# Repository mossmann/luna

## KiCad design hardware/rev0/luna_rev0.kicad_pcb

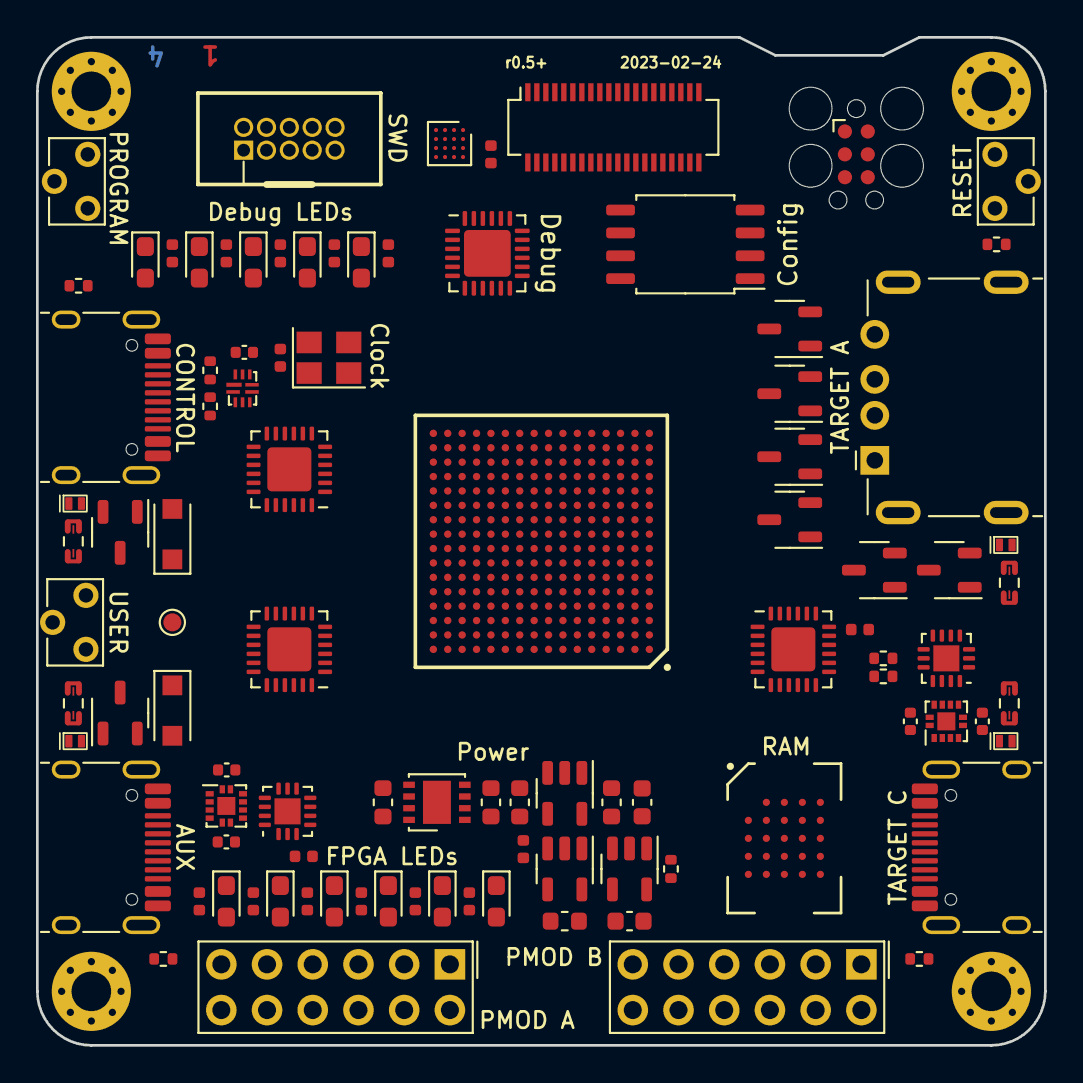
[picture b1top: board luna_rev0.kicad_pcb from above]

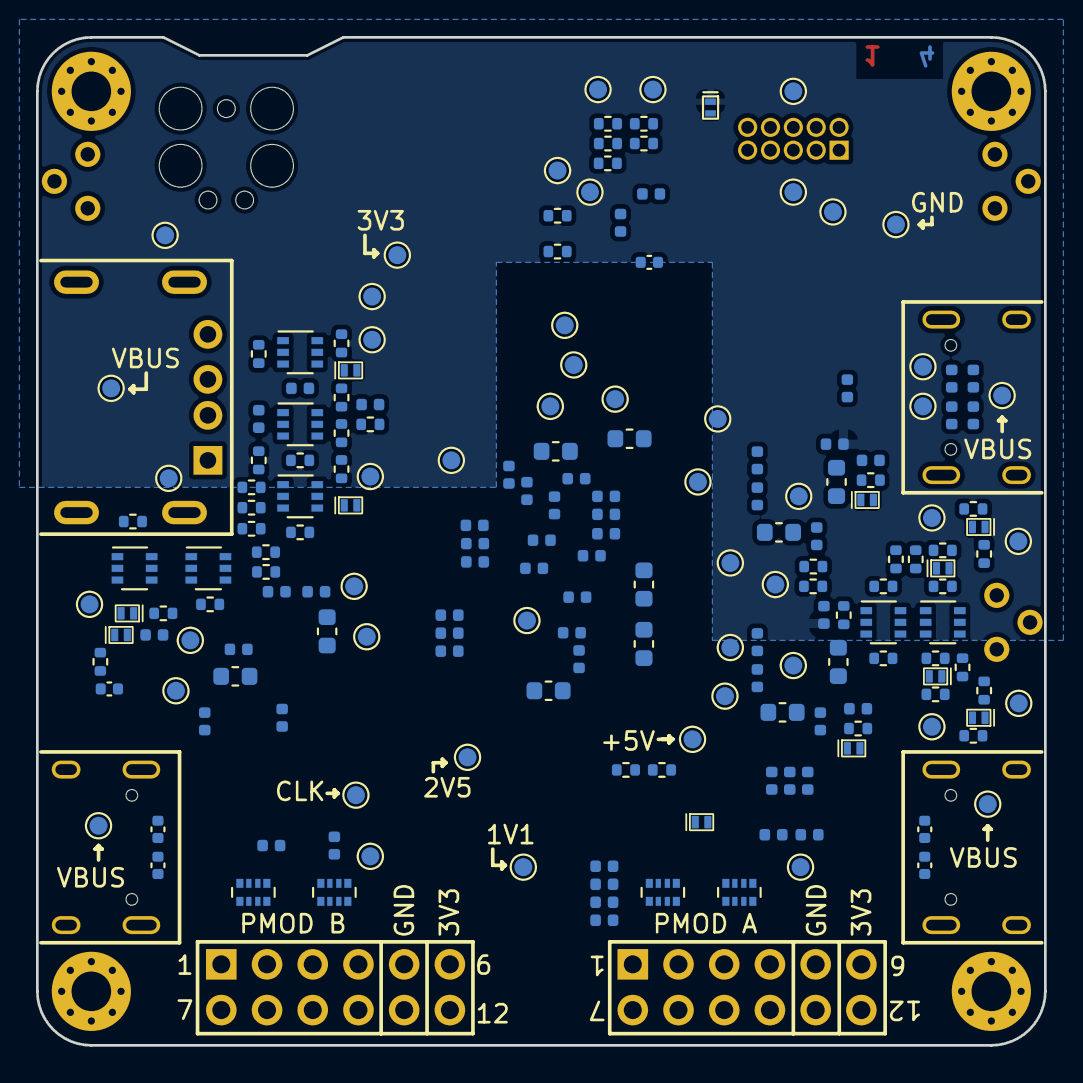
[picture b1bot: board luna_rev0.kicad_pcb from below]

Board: 4 copper layers, 56.0 x 56.0 mm, 291 parts (190 on the bottom side), 260 nets, no tracks yet.

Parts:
C1, C2, C3, C4, C20: 2.2uF; C_0603_1608Metric
C5, C7, C8, C9, C10, C11, C12, C13, C14, C15, C16, C17, C18, C19, C21, C23, C24, C26, C27, C31, C32, C33, C34, C35, C38, C39, C41, C44, C46, C49, C56, C57, C58, C61, C63: 0.1uF; C_0402_1005Metric
C6, C22, C28, C29, C30, C36, C37, C42, C43, C48, C50, C59, C60: 1uF; C_0603_1608Metric
C25, C47, C52, C53, C54, C55: 390pF; C_0402_1005Metric
C40, C45, C51: C; C_0402_1005Metric
C62: 1nF; C_0402_1005Metric
D1, D8: D; D_SOD-123F
D2: RED; LED_0603_1608Metric_Pad1.05x0.95mm_HandSolder
D3: ORANGE; LED_0603_1608Metric_Pad1.05x0.95mm_HandSolder
D4: YELLOW; LED_0603_1608Metric_Pad1.05x0.95mm_HandSolder
D5: GREEN; LED_0603_1608Metric_Pad1.05x0.95mm_HandSolder
D6: BLUE; LED_0603_1608Metric_Pad1.05x0.95mm_HandSolder
D7: PURPLE; LED_0603_1608Metric_Pad1.05x0.95mm_HandSolder
D9: PMEG4010ESBYL; DSN1006-2
D10, D14: ICE BLUE; LED_0603_1608Metric_Pad1.05x0.95mm_HandSolder
D11, D13: PINK; LED_0603_1608Metric_Pad1.05x0.95mm_HandSolder
D12: WHITE; LED_0603_1608Metric_Pad1.05x0.95mm_HandSolder
D15, D18, D22: 24±2%; DFN1006-2
D16, D20: 18±2%; DFN1006-2
D17, D21: 5.6±2%; DFN1006-2
D19, D27, D28, D29: 6.2±2%; DFN1006-2
D23, D24, D25, D26: TVS; DFN1006-2
H1, H2, H3, H4: MountingHole; MountingHole_2.2mm_M2_Pad_Via
IC1: ECP5-BGA256; lattice_cabga256
J1, J2, J4: USB_C_Receptacle_USB2.0; USB_C_Receptacle_HRO_TYPE-C-31-M-12
J3: USB_A; USB_A_Kycon_KUSBXHT-SB-AS1N-B30-NF_Horizontal
J6: MCU_SWD; SWD_CONNECTOR_LARGE_BOX
J7: PMOD_A; PinSocket_2x06_P2.54mm_PMOD
J8: PMOD_B; PinSocket_2x06_P2.54mm_PMOD
J9: Molex_SlimStack_55560-0401_2x20_P0.50mm_Vertical
J10: TC_SWD; Tag-Connect_TC2030-IDC-FP_2x03_P1.27mm_Vertical
Q1, Q2, Q4, Q5, Q6, Q7, Q9, Q12: PMOS; SOT-23-3
Q3, Q8, Q11: 2NPN; SOT-363_SC-70-6
Q10, Q13, Q14, Q15: 2PNP; SOT-363_SC-70-6
R1, R2, R42, R59: 0.02±1%; R_0603_1608Metric_Current_Sense
R3, R47, R48, R49, R60, R61, R69, R70, R76, R77: 33k; R_0402_1005Metric
R4, R32, R36, R43, R50, R51, R54: 0; R_0402_1005Metric
R5, R8, R9, R10, R30, R31, R33, R38, R40, R63, R65, R71, R78, R83, R84, R88: 2.2k; R_0402_1005Metric
R6, R12, R13, R14, R15, R22, R23, R24, R25, R29, R37, R39, R41, R52, R53, R64, R66, R72, R79, R85, R86, R87, R89: 10k; R_0402_1005Metric
R7, R11, R34, R35, R44, R45, R46: 5.1k; R_0402_1005Metric
R16, R18, R20: 8.06k±1%; R_0402_1005Metric
R17, R19, R21: 20k; R_0402_1005Metric
R26, R27, R28, R57, R58: 1k; R_0402_1005Metric
R55, R56, R68, R75: 820k; R_0402_1005Metric
R62, R90, R91, R92, R93, R94, R95, R96: 100k; R_0402_1005Metric
R67, R73, R74, R80, R82: 18.7k±1%; R_0402_1005Metric
R81: 58.3k±1%; R_0402_1005Metric
RN1, RN2, RN3, RN4: 33; R_Array_Convex_4x0402
SW1: BTN_PROGRAM; SW_Tactile_SPST_Angled_TC-1109DE-B-F
SW2: BTN_RESET; SW_Tactile_SPST_Angled_TC-1109DE-B-F
SW3: BTN_USER; SW_Tactile_SPST_Angled_TC-1109DE-B-F
TP1, TP2, TP3, TP4, TP5, TP6, TP7, TP8, TP9, TP10, TP11, TP12, TP13, TP14, TP15, TP16, TP17, TP18, TP19, TP20, TP21, TP22, TP23, TP24, TP25, TP26, TP27, TP28, TP29, TP30, TP31, TP32, TP33, TP34, TP35, TP36, TP37, TP38, TP39, TP40, TP42, TP43, TP44, TP45, TP46, TP47, TP48, TP49, TP50, TP51: TestPoint; TestPoint_Pad_D1.0mm
U1: PAC195X-1-WLCSP; WLCSP-16_2.225x2.170mm_Layout4x4_P0.5mm
U2, U12: FUSB302BMPX; WQFN-14-1EP_2.5x2.5mm_P0.5mm_EP1.45x1.45mm
U3: AP7361EA-33; DFN-8-1EP_3x3mm_P0.65mm_EP1.55x2.4mm
U4: TCR2EF115; SOT-23-5
U5: MIC5504-2.5YM5; SOT-23-5
U6: ATSAMD11D14A-MUT; QFN-24-1EP_4x4mm_P0.5mm_EP2.6x2.6mm
U7: W25Q32JVSS; SOIC-8_5.23x5.23mm_P1.27mm
U8, U9, U11: USB3343-CP; VQFN-24-1EP_4x4mm_P0.5mm_EP2.45x2.45mm
U10: HyperRAM; BGA-24_5x5_6.0x8.0mm
U13, U14: DPO2036; Diodes_UQFN2020-12_Type-B
U15: MIC5504-1.8YM5; SOT-23-5
U16: PI3USB102G; Diodes_10-TQFN_ZL
Y1: Osc60MHz; Crystal_SMD_3225-4Pin_3.2x2.5mm

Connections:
+1V1: C1.1, C3.1, C7.1, C9.1, C11.1, C13.1, C15.1, C17.1, C29.1, IC1.G6 (VCC_1), IC1.G7 (VCC_2), IC1.G9 (VCC_3), IC1.L8 (VCC_4), IC1.L9 (VCC_5), IC1.L10 (VCC_6), TP4.1, U4.5 (VOUT), U6.3 (PA04)
+2V5: C22.1, C24.1, C26.1, C27.1, C30.1, IC1.G11 (VCCAUX_1), IC1.L7 (VCCAUX_2), TP5.1, U4.1 (VIN), U4.3 (EN), U5.5 (VOUT), U6.2 (PA03)
+3V3: C2.1, C4.1, C8.1, C10.1, C12.1, C14.1, C16.1, C18.1, C20.1, C28.1, C33.1, C34.1, C35.1, C39.1, C40.1, C41.1, C49.1, C56.1, C58.1, C59.1, C61.1, D2.2 (A), D3.2 (A), D4.2 (A), D5.2 (A), D6.2 (A), D7.2 (A), D10.2 (A), D11.2 (A), D12.2 (A), D13.2 (A), D14.2 (A), IC1.F6 (VCCIO0_1), IC1.F7 (VCCIO0_2), IC1.F10 (VCCIO1_1), IC1.F11 (VCCIO1_2), IC1.H11 (VCCIO2_1), IC1.J6 (VCCIO6_1), IC1.J7 (VCCIO6_2), IC1.J11 (VCCIO2_2), IC1.K11 (VCCIO3_1), IC1.L6 (VCCIO8), IC1.L11 (VCCIO3_2), J6.1 (VTref), J7.6, J7.12, J8.6, J8.12, J10.1, R6.1, R13.2, R25.1, R32.2, R33.1, R36.2, R37.1, R38.1, R39.1, R52.1, R54.1, R81.1, R83.1, R84.1, R85.1, R86.1, R87.1, TP3.1, U1.A4 (VDD), U2.3 (VDD), U2.4 (VDD), U3.1 (OUT), U5.1 (VIN), U5.3 (EN), U6.24 (VDD), U7.8 (VCC), U8.2 (CLKOUT), U8.9 (VDDIO), U8.18 (ID), U9.2 (CLKOUT), U9.9 (VDDIO), U9.18 (ID), U11.2 (CLKOUT), U11.9 (VDDIO), U11.18 (ID), U12.3 (VDD), U12.4 (VDD), U13.12 (VSYS), U14.12 (VSYS), U15.1 (VIN), U15.3 (EN), U16.9 (VCC), Y1.1 (EN), Y1.4 (VDD)
+5V: C6.1, C38.1, C44.1, C46.1, D1.1 (K), D8.1 (K), D9.1 (K), D19.1 (K), TP30.1, TP49.1, U3.5 (EN), U3.8 (IN), U8.16 (VBAT), U9.16 (VBAT), U11.16 (VBAT)
/AUX Port/AUX.CLK: IC1.J16 (PR23A), TP32.1, U11.21 (REFCLK/XI)
/AUX Port/AUX.DATA0: IC1.F16 (PR14A), U11.4 (DATA0)
/AUX Port/AUX.DATA1: IC1.F15 (PR11C), U11.5 (DATA1)
/AUX Port/AUX.DATA2: IC1.E16 (PR11D), U11.6 (DATA2)
/AUX Port/AUX.DATA3: IC1.E15 (PR8B), U11.7 (DATA3)
/AUX Port/AUX.DATA4: IC1.D16 (PR8A), U11.8 (DATA4)
/AUX Port/AUX.DATA5: IC1.E14 (PR5C), U11.10 (DATA5)
/AUX Port/AUX.DATA6: IC1.F13 (PR8C), U11.11 (DATA6)
/AUX Port/AUX.DATA7: IC1.F12 (PR8D), U11.12 (DATA7)
/AUX Port/AUX.DIR: IC1.G16 (PR20A), U11.1 (DIR)
/AUX Port/AUX.NXT: IC1.G15 (PR14B), U11.3 (NXT)
/AUX Port/AUX.STP: IC1.H15 (PR20B), U11.24 (STP)
/AUX Port/AUX.~RESET: IC1.J15 (PR23B), R24.1, TP33.1, U11.22 (RESET)
/AUX Port/AUX_CC1: C52.1, J1.A5 (CC1), U14.3 (CC1C)
/AUX Port/AUX_CC1S: U12.10 (CC1), U12.11 (CC1), U14.8 (CC1S)
/AUX Port/AUX_CC2: C53.1, J1.B5 (CC2), U14.4 (CC2C)
/AUX Port/AUX_CC2S: U12.1 (CC2), U12.14 (CC2), U14.7 (CC2S)
/AUX Port/AUX_D+: J1.A6 (D+), J1.B6 (D+), U11.14 (D+)
/AUX Port/AUX_D-: J1.A7 (D-), J1.B7 (D-), U11.13 (D-)
/AUX Port/AUX_PHY_1V8: C50.1, TP35.1, U11.23 (VDD18)
/AUX Port/AUX_SBU1: J1.A8 (SBU1), U14.2 (SBU2C)
/AUX Port/AUX_SBU1S: IC1.D14 (PR2D), U14.10 (SBU1S)
/AUX Port/AUX_SBU2: J1.B8 (SBU2), U14.1 (SBU1C)
/AUX Port/AUX_SBU2S: IC1.C16 (PR5A), U14.9 (SBU2S)
/AUX Port/AUX_SCL: IC1.B15 (PR2B), R38.2, U12.6 (SCL)
/AUX Port/AUX_SDA: IC1.B16 (PR2A), R33.2, U12.7 (SDA)
/AUX Port/AUX_VBUS: D25.1 (K), J1.A4 (VBUS), J1.A9 (VBUS), J1.B4 (VBUS), J1.B9 (VBUS), R42.4, R44.2, TP34.1
/AUX Port/AUX_VCONN: C51.1, R32.1, TP37.1, U12.12 (VCONN), U12.13 (VCONN)
/AUX Port/~AUX_FAULT: IC1.C15 (PR5B), U14.6 (FAULTB)
/AUX Port/~AUX_INT: IC1.C14 (PR2C), R39.2, U12.5 (INT_N)
/AUX Port/~AUX_VBUS_IN_EN: IC1.J14 (PR20C), R78.2, TP48.1
/AUX Port/~CONTROL_VBUS_IN_EN: IC1.K14 (PR20D), R71.2, TP45.1
/CONTROL Port/CONTROL.CLK: IC1.R12 (PR44A), TP2.1, U8.21 (REFCLK/XI)
/CONTROL Port/CONTROL.DATA0: IC1.R16 (PR35B), U8.4 (DATA0)
/CONTROL Port/CONTROL.DATA1: IC1.P14 (PR38B), U8.5 (DATA1)
/CONTROL Port/CONTROL.DATA2: IC1.P16 (PR35A), U8.6 (DATA2)
/CONTROL Port/CONTROL.DATA3: IC1.P15 (PR32B), U8.7 (DATA3)
/CONTROL Port/CONTROL.DATA4: IC1.N16 (PR32A), U8.8 (DATA4)
/CONTROL Port/CONTROL.DATA5: IC1.M15 (PR26D), U8.10 (DATA5)
/CONTROL Port/CONTROL.DATA6: IC1.M16 (PR26C), U8.11 (DATA6)
/CONTROL Port/CONTROL.DATA7: IC1.L15 (PR26B), U8.12 (DATA7)
/CONTROL Port/CONTROL.DIR: IC1.T15 (PR38D), U8.1 (DIR)
/CONTROL Port/CONTROL.NXT: IC1.R15 (PR38C), U8.3 (NXT)
/CONTROL Port/CONTROL.STP: IC1.T13 (PR44B), U8.24 (STP)
/CONTROL Port/CONTROL.~RESET: IC1.N12 (PR44D), R22.1, TP15.1, U8.22 (RESET)
/CONTROL Port/CONTROL_CC1: C25.1, J2.A5 (CC1), R34.2, TP39.1
/CONTROL Port/CONTROL_CC2: C47.1, J2.B5 (CC2), R35.2, TP38.1
/CONTROL Port/CONTROL_D+: J2.A6 (D+), J2.B6 (D+), R55.1, U16.1 (D+)
/CONTROL Port/CONTROL_D-: J2.A7 (D-), J2.B7 (D-), R56.2, U16.2 (D-)
/CONTROL Port/CONTROL_FPGA_D+: U8.14 (D+), U16.7 (2D+)
/CONTROL Port/CONTROL_FPGA_D-: U8.13 (D-), U16.6 (2D-)
/CONTROL Port/CONTROL_MCU_D+: U6.22 (PA25), U16.5 (1D+)
/CONTROL Port/CONTROL_MCU_D-: U6.21 (PA24), U16.4 (1D-)
/CONTROL Port/CONTROL_PHY_1V8: C37.1, TP17.1, U8.23 (VDD18)
/CONTROL Port/CONTROL_RESET_DETECT: C62.1, R55.2, R56.1, U6.4 (PA05)
/CONTROL Port/CONTROL_SWITCH: R15.1, U6.8 (PA09/XOUT), U16.10 (S)
/CONTROL Port/CONTROL_VBUS: D23.1 (K), J2.A4 (VBUS), J2.A9 (VBUS), J2.B4 (VBUS), J2.B9 (VBUS), R1.1, R46.2, TP16.1
/CONTROL Port/CONTROL_VBUS_CLAMPED: D22.1 (K), R17.1, R46.1
/CONTROL Port/~FPGA_SELF_PROGRAM: IC1.P13 (PR41A), R5.2
/Clock and Pmod/CLKIN_60MHZ: IC1.A8 (PT29B), TP1.1, Y1.3 (OUT)
/Debugger and FPGA Configuration/D0: IC1.T8 (D0/PICO/PB11B), U7.5 (DI(IO0))
/Debugger and FPGA Configuration/D1: IC1.T7 (D1/PICO/PB11A), U7.2 (DO(IO1))
/Debugger and FPGA Configuration/D2: IC1.M7 (D2/PB9B), U7.3 (IO2)
/Debugger and FPGA Configuration/D3: IC1.N7 (D3/PB9A), U7.7 (IO3)
/Debugger and FPGA Configuration/FPGA_CFG0: IC1.N10 (CFG_0), R12.1
/Debugger and FPGA Configuration/FPGA_CFG1: IC1.P10 (CFG_1), R13.1
/Debugger and FPGA Configuration/FPGA_CFG2: IC1.R10 (CFG_2), R14.1
/Debugger and FPGA Configuration/FPGA_CONFIG_CLK: IC1.N9 (MCLK/SCLK/CCLK), TP10.1, U7.6 (CLK)
/Debugger and FPGA Configuration/FPGA_DONE: IC1.P9 (DONE), TP12.1
/Debugger and FPGA Configuration/FPGA_INT: IC1.R6 (D6/PB4B), U6.5 (PA06)
/Debugger and FPGA Configuration/FPGA_TCK: IC1.T10 (TCK), TP21.1, U6.12 (PA15)
/Debugger and FPGA Configuration/FPGA_TDI: IC1.H14 (PR14D), IC1.R11 (TDI), TP24.1, U6.11 (PA14)
/Debugger and FPGA Configuration/FPGA_TDO: IC1.M10 (TDO), TP23.1, U6.9 (PA10)
/Debugger and FPGA Configuration/FPGA_TMS: IC1.H13 (PR17B), IC1.T11 (TMS), TP22.1, U6.10 (PA11)
/Debugger and FPGA Configuration/MCU_SWDCLK: J6.4 (SWDCLK/TCK), J10.4, TP19.1, U6.19 (PA30/SWCLK)
/Debugger and FPGA Configuration/MCU_SWDIO: J6.2 (SWDIO/TMS), J10.2, TP20.1, U6.20 (PA31/SWDIO)
/Debugger and FPGA Configuration/~BTN_PROGRAM: SW1.1 (A), U6.1 (PA02)
/Debugger and FPGA Configuration/~BTN_RESET: J6.10 (~RESET), J10.3, R25.2, SW2.1 (A), TP18.1, U6.18 (PA28/~RST)
/Debugger and FPGA Configuration/~BTN_USER: IC1.T6 (D7/PB4A), SW3.1 (A)
/Debugger and FPGA Configuration/~CS_DI: IC1.N8 (HOLDN/DI/PB15A), TP11.1, U7.1 (~CS)
/Debugger and FPGA Configuration/~FPGA_INIT: IC1.T9 (INITN), TP13.1
/Debugger and FPGA Configuration/~FPGA_PROGRAM: IC1.R9 (PROGRAMN), R5.1, R6.2, TP14.1, U6.7 (PA08/XIN)
/LEDs and Pmod/LED0: IC1.E11 (PT51B), R31.2
/LEDs and Pmod/LED1: IC1.D10 (PT47A), R30.2
/LEDs and Pmod/LED2: IC1.A10 (PT42B), R29.2
/LEDs and Pmod/LED3: IC1.E10 (PT47B), R28.2
/LEDs and Pmod/LED4: IC1.A11 (PT53A), R27.2
/LEDs and Pmod/LED5: IC1.A12 (PT53B), R26.2
/PMOD_A0: J7.1, RN1.8 (R1.2)
/PMOD_A1: J7.2, RN1.7 (R2.2)
/PMOD_A2: J7.3, RN1.6 (R3.2)
/PMOD_A3: J7.4, RN1.5 (R4.2)
/PMOD_A4: C23.1, J7.7, RN2.5 (R4.2)
/PMOD_A5: C21.2, J7.8, RN2.6 (R3.2)
/PMOD_A6: C19.1, J7.9, RN2.8 (R1.2)
/PMOD_A7: C5.2, J7.10, RN2.7 (R2.2)
/PMOD_B0: J8.1, RN3.8 (R1.2)
/PMOD_B1: J8.2, RN3.7 (R2.2)
/PMOD_B2: J8.3, RN3.5 (R4.2)
/PMOD_B3: J8.4, RN4.7 (R2.2)
/PMOD_B4: J8.7, RN3.6 (R3.2)
/PMOD_B5: J8.8, RN4.8 (R1.2)
/PMOD_B6: J8.9, RN4.6 (R3.2)
/PMOD_B7: J8.10, RN4.5 (R4.2)
/Power Distribution and Monitoring/AUX_VBUS_EN: IC1.T3 (PL41D), R63.2
/Power Distribution and Monitoring/CONTROL_VBUS_EN: IC1.R4 (PL41C), R40.2
/Power Distribution and Monitoring/GPIO/~ALERT2: IC1.M5 (PL44C), R86.2, U1.B2 (GPIO/~ALERT2)
/Power Distribution and Monitoring/SCL: IC1.L2 (PL26B), R83.2, TP50.1, U1.C4 (SCL), U2.6 (SCL)
/Power Distribution and Monitoring/SDA: IC1.L1 (PL26A), R84.2, TP51.1, U1.D4 (SDA), U2.7 (SDA)
/Power Distribution and Monitoring/SLOW/~ALERT: IC1.T4 (PL44B), R85.2, U1.C3 (SLOW/~ALERT)
/Power Distribution and Monitoring/TARGET_A_DISCHARGE: IC1.P5 (PL47D), R88.2
/Power Distribution and Monitoring/TARGET_A_VBUS: D24.1 (K), J3.1 (VBUS), R2.4, TP7.1
/Power Distribution and Monitoring/TARGET_C_VBUS: D26.1 (K), J4.A4 (VBUS), J4.A9 (VBUS), J4.B4 (VBUS), J4.B9 (VBUS), R45.2, R59.4, TP40.1
/Power Distribution and Monitoring/~PWRDN: IC1.N5 (PL44D), R87.2, U1.B3 (~PWRDN)
/Power Distribution and Monitoring/~TARGET_C_VBUS_EN: IC1.P6 (PL47C), R65.2
/RAM/RAM.CK: IC1.F4 (PL8C), U10.B2 (CK)
/RAM/RAM.DQ0: IC1.C2 (PL5B), U10.D3 (DQ0)
/RAM/RAM.DQ1: IC1.D3 (PL2D), U10.D2 (DQ1)
/RAM/RAM.DQ2: IC1.F3 (PL5D), U10.C4 (DQ2)
/RAM/RAM.DQ3: IC1.E3 (PL5C), U10.D4 (DQ3)
/RAM/RAM.DQ4: IC1.C1 (PL5A), U10.D5 (DQ4)
/RAM/RAM.DQ5: IC1.C3 (PL2C), U10.E3 (DQ5)
/RAM/RAM.DQ6: IC1.B1 (PL2A), U10.E2 (DQ6)
/RAM/RAM.DQ7: IC1.B2 (PL2B), U10.E1 (DQ7)
/RAM/RAM.RWDS: IC1.D1 (PL8A), U10.C3 (RWDS)
/RAM/RAM.~CK: IC1.F5 (PL8D), U10.B1 (~CK)
/RAM/RAM.~CS: IC1.E2 (PL8B), U10.A3 (~CS)
/RAM/RAM.~RESET: IC1.G5 (PL11A), U10.A4 (~RESET)
/TARGET Port/TARGET.CLK: IC1.P1 (PL35A), TP26.1, U9.21 (REFCLK/XI)
/TARGET Port/TARGET.DATA0: IC1.N3 (PL35D), U9.4 (DATA0)
/TARGET Port/TARGET.DATA1: IC1.L5 (PL29D), U9.5 (DATA1)
/TARGET Port/TARGET.DATA2: IC1.N4 (PL38A), U9.6 (DATA2)
/TARGET Port/TARGET.DATA3: IC1.M4 (PL35C), U9.7 (DATA3)
/TARGET Port/TARGET.DATA4: IC1.P4 (PL41A), U9.8 (DATA4)
/TARGET Port/TARGET.DATA5: IC1.P3 (PL38B), U9.10 (DATA5)
/TARGET Port/TARGET.DATA6: IC1.R3 (PL41B), U9.11 (DATA6)
/TARGET Port/TARGET.DATA7: IC1.M6 (PL47A), U9.12 (DATA7)
/TARGET Port/TARGET.DIR: IC1.N1 (PL32A), U9.1 (DIR)
/TARGET Port/TARGET.NXT: IC1.P2 (PL32B), U9.3 (NXT)
/TARGET Port/TARGET.STP: IC1.L3 (PL32C), U9.24 (STP)
/TARGET Port/TARGET.~RESET: IC1.M3 (PL32D), R23.1, TP25.1, U9.22 (RESET)
/TARGET Port/TARGET_CC1: C54.1, J4.A5 (CC1), U13.3 (CC1C)
/TARGET Port/TARGET_CC1S: U2.10 (CC1), U2.11 (CC1), U13.8 (CC1S)
/TARGET Port/TARGET_CC2: C55.1, J4.B5 (CC2), U13.4 (CC2C)
/TARGET Port/TARGET_CC2S: U2.1 (CC2), U2.14 (CC2), U13.7 (CC2S)
/TARGET Port/TARGET_D+: J3.3 (D+), J4.A6 (D+), J4.B6 (D+), R58.1, U9.14 (D+)
/TARGET Port/TARGET_D-: J3.2 (D-), J4.A7 (D-), J4.B7 (D-), R57.1, U9.13 (D-)
/TARGET Port/TARGET_FS_MONITOR_D+: IC1.T2 (PL38D), R58.2
/TARGET Port/TARGET_FS_MONITOR_D-: IC1.R2 (PL38C), R57.2
/TARGET Port/TARGET_PHY_1V8: C43.1, TP27.1, U9.23 (VDD18)
/TARGET Port/TARGET_SBU1: J4.A8 (SBU1), U13.1 (SBU1C)
/TARGET Port/TARGET_SBU1S: IC1.M2 (PL26D), U13.10 (SBU1S)
/TARGET Port/TARGET_SBU2: J4.B8 (SBU2), U13.2 (SBU2C)
/TARGET Port/TARGET_SBU2S: IC1.K4 (PL29A), U13.9 (SBU2S)
/TARGET Port/TARGET_VCONN: C45.1, R36.1, TP36.1, U2.12 (VCONN), U2.13 (VCONN)
/TARGET Port/~TARGET_FAULT: IC1.K5 (PL29B), U13.6 (FAULTB)
/TARGET Port/~TARGET_INT: IC1.M1 (PL26C), R37.2, U2.5 (INT_N)
AUX_SENSE+: R42.3, U1.A3 (SENSE1+)
AUX_SENSE-: R42.2, U1.A2 (SENSE1-)
AUX_VBUS_CLAMPED: D15.1 (K), R21.1, R44.1, U12.2 (VBUS)
AUX_VBUS_IN: D20.1 (K), Q4.3 (D), Q10.4 (E2), Q12.2 (S), R42.1, R74.1, R75.1
CONTROL_SENSE+: R1.2, U1.A1 (SENSE2+)
CONTROL_SENSE-: R1.3, U1.B1 (SENSE2-)
CONTROL_VBUS_IN: D16.1 (K), Q1.3 (D), Q9.2 (S), Q10.1 (E1), R1.4, R67.1, R68.1
GND: C1.2, C2.2, C3.2, C4.2, C6.2, C7.2, C8.2, C9.2, C10.2, C11.2, C12.2, C13.2, C14.2, C15.2, C16.2, C17.2, C18.2, C20.2, C22.2, C24.2, C25.2, C26.2, C27.2, C28.2, C29.2, C30.2, C31.2, C32.2, C33.2, C34.2, C35.2, C36.2, C37.2, C38.2, C39.2, C40.2, C41.2, C42.2, C43.2, C44.2, C45.2, C46.2, C47.2, C48.2, C49.2, C50.2, C51.2, C52.2, C53.2, C54.2, C55.2, C56.2, C57.2, C58.2, C59.2, C60.2, C61.2, C62.2, C63.2, D15.2 (A), D18.2 (A), D19.2 (A), D22.2 (A), D23.2 (A), D24.2 (A), D25.2 (A), D26.2 (A), H1.1, H2.1, H3.1, H4.1, IC1.A1 (GND_1), IC1.A16 (GND_2), IC1.D2 (GND_3), IC1.D15 (GND_4), IC1.F8 (GND_5), IC1.F9 (GND_6), IC1.G8 (GND_7), IC1.G10 (GND_8), IC1.H1 (GND_9), IC1.H8 (GND_10), IC1.H9 (GND_11), IC1.H10 (GND_12), IC1.H16 (GND_13), IC1.J8 (GND_14), IC1.J9 (GND_15), IC1.J10 (GND_16), IC1.K6 (GND_17), IC1.K7 (GND_18), IC1.K8 (GND_19), IC1.K9 (GND_20), IC1.K10 (GND_21), IC1.N2 (GND_22), IC1.N15 (GND_23), IC1.T1 (GND_24), IC1.T5 (GND_25), IC1.T12 (GND_26), IC1.T16 (GND_27), J1.A1 (GND), J1.A12 (GND), J1.B1 (GND), J1.B12 (GND), J2.A1 (GND), J2.A12 (GND), J2.B1 (GND), J2.B12 (GND), J3.4 (GND), J4.A1 (GND), J4.A12 (GND), J4.B1 (GND), J4.B12 (GND), J6.3 (GND), J6.5 (GND), J6.9 (GNDDetect), J7.5, J7.11, J8.5, J8.11, J10.5, Q3.1 (E1), Q3.4 (E2), Q8.1 (E1), Q8.4 (E2), Q11.1 (E1), Q11.4 (E2), R4.1, R12.2, R14.2, R15.2, R16.1, R18.1, R20.1, R22.2, R23.2, R24.2, R34.1, R35.1, R41.2, R43.2, R50.1, R51.2, R53.2, R64.2, R66.2, R70.2, R72.2, R73.2, R77.2, R79.2, R80.2, R82.2, R89.2, R90.1, R91.1, R94.1, R95.1, R96.1, SW1.2 (B), SW2.2 (B), SW3.2 (B), TP28.1, U1.B4 (GND), U1.C2 (ADDRSEL), U2.8 (GND), U2.9 (GND), U2.15 (GND), U3.4 (GND), U3.9 (GND), U4.2 (GND), U5.2 (GND), U6.23 (GND), U7.4 (GND), U8.25 (GND), U9.25 (GND), U10.B3 (VSS), U10.C1 (VSSQ), U10.E5 (VSSQ), U11.25 (GND), U12.8 (GND), U12.9 (GND), U12.15 (GND), U13.11 (GND), U13.13 (GND), U14.11 (GND), U14.13 (GND), U15.2 (GND), U16.3 (GND), U16.8 (~OE), Y1.2 (GND)
unnamed: C5.1, IC1.A14 (PT65B), RN2.2 (R2.1)
unnamed: C19.2, IC1.A13 (PT65A), RN2.1 (R1.1)
unnamed: C21.1, IC1.B14 (PT67A), RN2.3 (R3.1)
unnamed: C23.2, IC1.A15 (PT67B), RN2.4 (R4.1)
unnamed: C36.1, U8.15 (VDD33)
unnamed: C42.1, U9.15 (VDD33)
unnamed: C48.1, U11.15 (VDD33)
unnamed: C57.1, U13.5 (CB)
unnamed: C63.1, U14.5 (CB)
unnamed: D1.2 (A), Q12.3 (D)
unnamed: D2.1 (K), R26.1
unnamed: D3.1 (K), R27.1
unnamed: D4.1 (K), R28.1
unnamed: D5.1 (K), R29.1
unnamed: D6.1 (K), R30.1
unnamed: D7.1 (K), R31.1
unnamed: D8.2 (A), Q9.3 (D)
unnamed: D9.2 (A), J10.6
unnamed: D10.1 (K), R7.1
unnamed: D11.1 (K), R8.1
unnamed: D12.1 (K), R9.1
unnamed: D13.1 (K), R10.1
unnamed: D14.1 (K), R11.1
unnamed: D16.2 (A), Q9.1 (G), Q10.6 (C1), R68.2, R70.1, TP8.1
unnamed: D17.1 (K), R47.2, R67.2, R69.1, TP44.1
unnamed: D17.2 (A), R73.1
unnamed: D20.2 (A), Q10.3 (C2), Q12.1 (G), R75.2, R77.1, TP46.1
unnamed: D21.1 (K), R48.2, R74.2, R76.1, TP47.1
unnamed: D21.2 (A), R80.1
unnamed: D27.1 (K), Q1.2 (S), Q2.2 (S), Q13.1 (E1), Q13.4 (E2), R3.1
unnamed: D27.2 (A), Q1.1 (G), Q2.1 (G), Q13.6 (C1), R90.2, TP29.1
unnamed: D28.1 (K), Q4.2 (S), Q5.2 (S), Q14.1 (E1), Q14.4 (E2), R60.1
unnamed: D28.2 (A), Q4.1 (G), Q5.1 (G), Q14.6 (C1), R94.2, TP31.1
unnamed: D29.1 (K), Q6.2 (S), Q7.2 (S), Q15.1 (E1), R61.1
unnamed: D29.2 (A), Q6.1 (G), Q7.1 (G), Q15.6 (C1), R96.2, TP42.1
unnamed: IC1.A3 (PT6A), RN3.1 (R1.1)
unnamed: IC1.A4 (PT6B), RN3.2 (R2.1)
unnamed: IC1.A5 (PT18A), RN3.4 (R4.1)
unnamed: IC1.A6 (PT18B), RN4.2 (R2.1)
unnamed: IC1.B6 (PT22B), RN4.1 (R1.1)
unnamed: IC1.B7 (PT27B), RN4.4 (R4.1)
unnamed: IC1.B13 (PT60A), RN1.1 (R1.1)
unnamed: IC1.C6 (PT22A), RN3.3 (R3.1)
unnamed: IC1.C7 (PT27A), RN4.3 (R3.1)
unnamed: IC1.C13 (PT60B), RN1.2 (R2.1)
unnamed: IC1.D13 (PT62A), RN1.3 (R3.1)
unnamed: IC1.E13 (PT62B), RN1.4 (R4.1)
unnamed: J1.S1 (SHIELD), R43.1
unnamed: J2.S1 (SHIELD), R51.1
unnamed: J3.5 (Shield), R4.2
unnamed: J4.S1 (SHIELD), R50.2
unnamed: Q3.2 (B1), R40.1, R41.1
unnamed: Q3.3 (C2), R60.2, R92.1
unnamed: Q3.5 (B2), R63.1, R64.1
unnamed: Q3.6 (C1), R3.2, R62.1
unnamed: Q8.2 (B1), R65.1, R66.1
unnamed: Q8.3 (C2), R49.2
unnamed: Q8.5 (B2), R88.1, R89.1
unnamed: Q8.6 (C1), R61.2, R93.1, TP43.1
unnamed: Q10.2 (B1), R47.1
unnamed: Q10.5 (B2), R48.1
unnamed: Q11.2 (B1), R71.1, R72.1
unnamed: Q11.3 (C2), R76.2
unnamed: Q11.5 (B2), R78.1, R79.1
unnamed: Q11.6 (C1), R69.2
unnamed: Q13.2 (B1), Q13.3 (C2), R91.2
unnamed: Q13.5 (B2), R62.2
unnamed: Q14.2 (B1), Q14.3 (C2), R95.2
unnamed: Q14.5 (B2), R92.2
unnamed: Q15.2 (B1), R93.2
unnamed: R7.2, U6.13 (PA16)
unnamed: R8.2, U6.14 (PA17)
unnamed: R9.2, U6.15 (PA22)
unnamed: R10.2, U6.16 (PA23)
unnamed: R11.2, U6.17 (PA27)
unnamed: R16.2, U8.19 (RBIAS)
unnamed: R17.2, U8.17 (VBUS)
unnamed: R18.2, U9.19 (RBIAS)
unnamed: R19.2, U9.17 (VBUS)
unnamed: R20.2, U11.19 (RBIAS)
unnamed: R21.2, U11.17 (VBUS)
unnamed: R52.2, R53.1, U6.6 (PA07)
unnamed: R81.2, R82.1, U3.3 (ADJ/NC)
TARGET_A_SENSE+: R2.3, U1.D3 (SENSE4+)
TARGET_A_SENSE-: R2.2, U1.D2 (SENSE4-)
TARGET_A_VBUS_IN: Q2.3 (D), Q5.3 (D), Q6.3 (D), R2.1, R49.1, TP9.1
TARGET_C_SENSE+: R59.3, U1.D1 (SENSE3+)
TARGET_C_SENSE-: R59.2, U1.C1 (SENSE3-)
TARGET_C_VBUS_CLAMPED: D18.1 (K), R19.1, R45.1, U2.2 (VBUS)
TARGET_C_VBUS_IN: Q7.3 (D), R59.1
VCCRAM: C31.1, C32.1, C60.1, IC1.H6 (VCCIO7_1), IC1.H7 (VCCIO7_2), R54.2, TP6.1, U10.B4 (VCC), U10.D1 (VCCQ), U10.E4 (VCCQ), U15.5 (VOUT)

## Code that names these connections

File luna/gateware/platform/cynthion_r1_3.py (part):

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        ),

        # power input shutoff
        Resource("control_vbus_in_en", 0, PinsN("K13", dir="o"), Attrs(IO_TYPE="LVCMOS33")),
        Resource("aux_vbus_in_en",     0, PinsN("L13", dir="o"), Attrs(IO_TYPE="LVCMOS33")),

        # VBUS passthrough
        #
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        # The TARGET C switch is enabled by default, even when Cynthion is
        # powered off, enabling VBUS passthrough from TARGET C to TARGET A.

        Resource("target_c_vbus_en",   0, PinsN("K5", dir="o"), Attrs(IO_TYPE="LVCMOS33", PULLMODE="UP")),
        Resource("control_vbus_en",    0, Pins("L1", dir="o"), Attrs(IO_TYPE="LVCMOS33")),
        Resource("aux_vbus_en",        0, Pins("L2", dir="o"), Attrs(IO_TYPE="LVCMOS33")),
        Resource("target_a_discharge", 0, Pins("K4", dir="o"), Attrs(IO_TYPE="LVCMOS33")),

        # voltage and current monitor
        Resource("power_monitor", 0,
            Subsignal("scl",   Pins( "D7", dir="o" ), Attrs(PULLMODE="NONE")),
            Subsignal("sda",   Pins( "C7", dir="io"), Attrs(PULLMODE="NONE")),
            Subsignal("pwrdn", PinsN("D5", dir="o" )),
            Subsignal("slow",  Pins( "C6", dir="io")),
            Subsignal("gpio",  Pins( "D6", dir="io")),
            Attrs(IO_TYPE="LVCMOS33", PULLMODE="UP")
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
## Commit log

2021-01-20 platforms: add support for LUNA r0.3
2023-01-19 hardware: update revision to r0.5+
2023-01-19 hardware: add FPGA bank outlines to Comments layer
2023-02-06 hardware: remove debug SPI interface
2023-02-06 hardware: update SPI signal names
    based on latest OSHWA guidance
2023-02-06 hardware: remove TARGET_VBUS_C measurement
2023-02-06 hardware: remove PHY 1.8 V measurement
2023-02-06 hardware: remove user i/o SMA connectors
2023-02-06 hardware: rename buses for KiCad 6
2023-02-06 hardware: correct or exclude all ERC errors
2023-02-06 hardware: use DNP field for DNP notation
2023-02-06 hardware: consistently use lowercase k for kilo
2023-02-07 hardware: correct or exclude all DRC errors
2023-02-07 hardware: shift absolute board position
2023-02-07 hardware: update mechanical design
    See Users.Drawings layer for dimensions and constraints. This breaks
    functionality of the layout. Function will be restored after upcoming
    changes to the schematic.
2023-02-14 hardware: add button BTN to FPGA
    intended for SoC reset or alternative FPGA use
2023-02-14 hardware: move DFU button to its own pin
    no longer shared with LED
2023-02-15 hardware: add 0 ohm resistors to USB shields
    provides ability to disconnect each shield from GND
2023-02-15 hardware: add mounting holes connected to GND
2023-02-15 hardware: add Pmod connector population note
    populate only when assembling for installation in enclosure
2023-02-15 hardware: move 2V5 measurement from PA07 to PA03
2023-02-15 hardware: add pin strap for version detection
2023-02-16 hardware: add FPGA interrupt
    allows FPGA to signal that it has something to say to the
    microcontroller
2023-02-16 hardware: migrate symbol libraries to KiCad 6
2023-02-16 hardware: restore 1.8 V RAM supply as an option
2023-02-16 hardware: reassign FPGA I/O banks
    assign HyperRAM to DQS group
2023-02-16 hardware: rename USB ports
    Sideband is renamed to Control and is intended for use as the primary
    control port for both the FPGA and the microcontroller/debugger.
    Host is renamed to Aux and is intended for auxiliary functions
    including MitM.
2023-02-16 hardware: rename schematic files
2023-02-16 hardware: add Control port USB switch
2023-02-17 hardware: add Control port reset detection
    USB reset can be detected by measuring the D+/D- common-mode voltage
    with the microcontroller's ADC or analog comparator.
2023-02-17 hardware: add Target D+/D- full-speed monitor
    allows FPGA to monitor low-speed or full-speed USB directly (instead of
    or in addition to the high-speed PHY)
2023-02-17 hardware: replace VBUS pass-through switches
    - increase maximum voltage with discrete FET solution
    - pass through Control and Aux VBUS directly, not +5V supply rail
    - add current sense resistors
    - eliminate discharge current of previous power switches
    - eliminate possible overvoltage condition of previous power switches
    - remove 10 uF VBUS output capacitor C53
2023-02-17 hardware: replace power input diodes
    - provide input selection capability with FETs
    - reduce reverse leakage current
    - provide overvoltage protection
2023-02-17 hardware: replace +3V3 regulator U3
    - support higher current
    - improve heat dissipation
2023-02-17 hardware: add VBUS voltage and current monitoring
2023-02-17 hardware: add Target port Type-C controller
    replaces buffers for CC pin I/O
2023-02-17 hardware: add Aux port Type-C controller
    replaces rudimentary CC pin input
2023-02-18 hardware: simplify Control port Type-C connections
    - remove CC/FPGA connections to ensure correct Rd is reliably present
    - remove SBU/FPGA connections to avoid need for ESD protection
    We provide CC and SBU pin access on the Target and Aux port. They are
    not necessary on the Control port. Simplification ensures reliability.
2023-02-18 hardware: clamp VBUS detection signals to 24 V
2023-02-18 hardware: add VBUS ESD protection
2023-02-21 hardware: protect CC and SBU pins
    add overvoltage and ESD protection for Aux port and Target port USB
    Type-C CC and SBU pins
2023-02-21 hardware: rename buttons
    DFU is now PROGRAM
    RST is now RESET
    BTN is now USER
2023-02-21 hardware: abbreviate microcontroller as MCU
2023-02-21 hardware: capitalize port names
2023-02-21 hardware: use "Exclude from bill of materials"
    Virtual components such as mounting holes and test points that do not
    require part placement now use this property instead of the DNP field.
2023-02-23 hardware: tune power input section
    - add base resistor to Q10A/Q10B PNP
    - adjust zener voltage
    - adjust zener series resistance
    - fix FET Q9/Q12 orientation
2023-02-24 hardware: improve VBUS pass-through
    - add gate drive to tolerate up to 40 V without exceeding FET Vgs limitation
    - add TARGET A discharge capability
2023-02-24 hardware: component placement
2023-02-24 hardware: remove FPGA JTAG connector J5
2023-02-24 hardware: use .step instead of .wrl 3D models
2023-03-09 hardware: update layout to match schematic
    - invert USB switch D+/D- for routing convenience
    - connect *_VBUS_CLAMPED to *_VBUS_IN not *_VBUS
    - reassign FPGA pins and banks for routing convenience
    - connect PHY VBAT to +3V3, not +5V
    - add PHY VDD33 test points
    - add LED test points
2023-03-11 hardware: passive component selection
2023-03-12 Back off AUX_VBUS_IN polygon from sensitive areas.
2023-03-12 Squashed commit of the following:
    commit 0e9b3443a5f0791f42246d75eaffd49ffb73ff13
    Author: Martin Ling <martin-git@earth.li>
    Date: Sat Mar 11 20:57:37 2023 +0000
    Second pass at silkscreen.
    commit bc39b31071113e5b4664c24391c16d3cbc8b2848
    Author: Martin Ling <martin-git@earth.li>
2023-03-12 hardware: improve silkscreen
    - use more of the space around the FPGA
    - use different line widths to distinguish connections from boundaries
    - use curved lines for more connections
    - move vias away from silkscreen
2023-03-12 hardware: add shield net
    - connect directly to mounting holes
    - connect to USB shields through 0 ohm resistors
    - connect to GND through 0 ohm resistor
2023-03-13 hardware: adjust silkscreen
2023-03-13 hardware: improve Type-C GND connections
2023-03-13 hardware: exclude DNP components from .pos files
2023-03-15 hardware: use short name in value field
2023-03-15 hardware: update PCB stackup specification
2023-04-07 hardware: make AUX SBU pin labels consistent
2023-04-08 hardware: correct ECP5-BGA256 pin T7 name
2023-04-16 hardware: update version to 0.6
2023-04-16 hardware: update version to 0.6+
2023-04-16 hardware: update component selections
    - fix overheating of TVS diodes D23-D26 starting at 27 V
    - change absolute maximum VBUS from 40 V to 30 V
2023-04-16 hardware: add RC filters to buttons
2023-04-17 hardware: update VBUS passthrough FETs
    - reduce on resistance
    - improve power dissipation
2023-04-17 hardware: update +5V input diodes
    improve power dissipation
2023-04-17 hardware: update current sense resistor footprint
    - use standard 0603 footprint for reliable assembly
2023-04-17 hardware: assign PCLK pin to mezzanine connector
    swap with PMOD A pins
2023-04-17 hardware: add series resistor to 60 MHz clock
2023-04-18 hardware: update pull-up and pull-down resistors
    - do not populate unnecessary resistors
    - remove some unnecessary 0 ohm resistors
    - add recommended FPGA resistors
    - add recommended MCU resistors
    - update hardware version detection pin strap
    - change CONTROL port USB switch default to MCU
2023-04-18 hardware: improve heat dissipation
2023-04-18 hardware: clean up fab layer
2023-04-18 hardware: update LED footprint
2023-04-18 hardware: update fabrication attributes
2023-04-18 hardware: update version to 0.7
2023-05-01 hardware: clean up schematic for readability
2023-05-01 hardware: update button RC filters for reliability
2023-05-01 hardware: update date
2023-05-01 hardware: update version to 0.7+
2023-05-01 hardware: update FET component selection
2023-05-01 hardware: fix via/silkscreen interference
2023-05-01 hardware: reduce paste area for 1006 diodes
2023-05-01 hardware: update version detection pin strap
2023-05-01 hardware: rename to Cynthion
2023-05-01 hardware: update version to 1.0.0
2023-05-04 hardware: rotate fab layer text
2023-05-04 hardware: nudge vias out of title silkscreen area
2023-05-17 hardware: adjust table in schematic
2023-05-17 hardware: update version to 1.0.0+
2023-05-18 hardware: change U1 from WLCSP to VQFN package
2023-05-18 hardware: increase minimum trace/space to 5 mil
2023-05-18 hardware: change FPGA_INT pin assignment
    This avoids an issue with FPGA_INT toggling during FPGA configuration.
2023-05-18 hardware: widen VCCRAM zone bottleneck at FPGA
2023-05-18 hardware: update version to 1.1.0
2023-06-06 hardware: update version to 1.1.1
    - adjust PROGRAM and RESET button placement to match USER button
2023-10-02 platforms: add Cynthion r1.3 support

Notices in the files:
luna/gateware/platform/cynthion_r1_3.py:
Copyright (c) 2020-2023 Great Scott Gadgets <info@greatscottgadgets.com>
SPDX-License-Identifier: BSD-3-Clause
hardware/rev0/luna_rev0.kicad_pcb:
Copyright 2019-2023 Great Scott Gadgets
Licensed under the CERN-OHL-P v2
